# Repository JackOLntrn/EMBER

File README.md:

# EMBER
## Overview
The EMBER project makes use of the a thermal IR camera to detect fires on a pan/tilt motor mechanism. Once a fire is detected, the system points the thermal camera/hose nozzle at the detected fire and activates a solenoid to spray water at the detected fire. The system is supplied with water from a garden hose. This repository includes all of the relavant files for the project. 
| Directory | Contents|
| --- | --- |
| [EMBER/src](src/) | Contains the header and cpp files developed for the project |
| [EMBER/hardware/board](hardware/board) | Contains the schematic board and gerber files used to develop a custom PCB used for the project|
| [EMBER/hardware/mech](hardware/mech) | Contains the 3D model files of parts developed for the project |
| [EMBER/docs](docs/) | Contains doxygen generated documents for code documentation |

See board documentation [here](hardware/board/README.md)

See mechanical component documentation [here](hardware/mech/README.md)

See code documentation [here](https://jackolntrn.github.io/EMBER/)

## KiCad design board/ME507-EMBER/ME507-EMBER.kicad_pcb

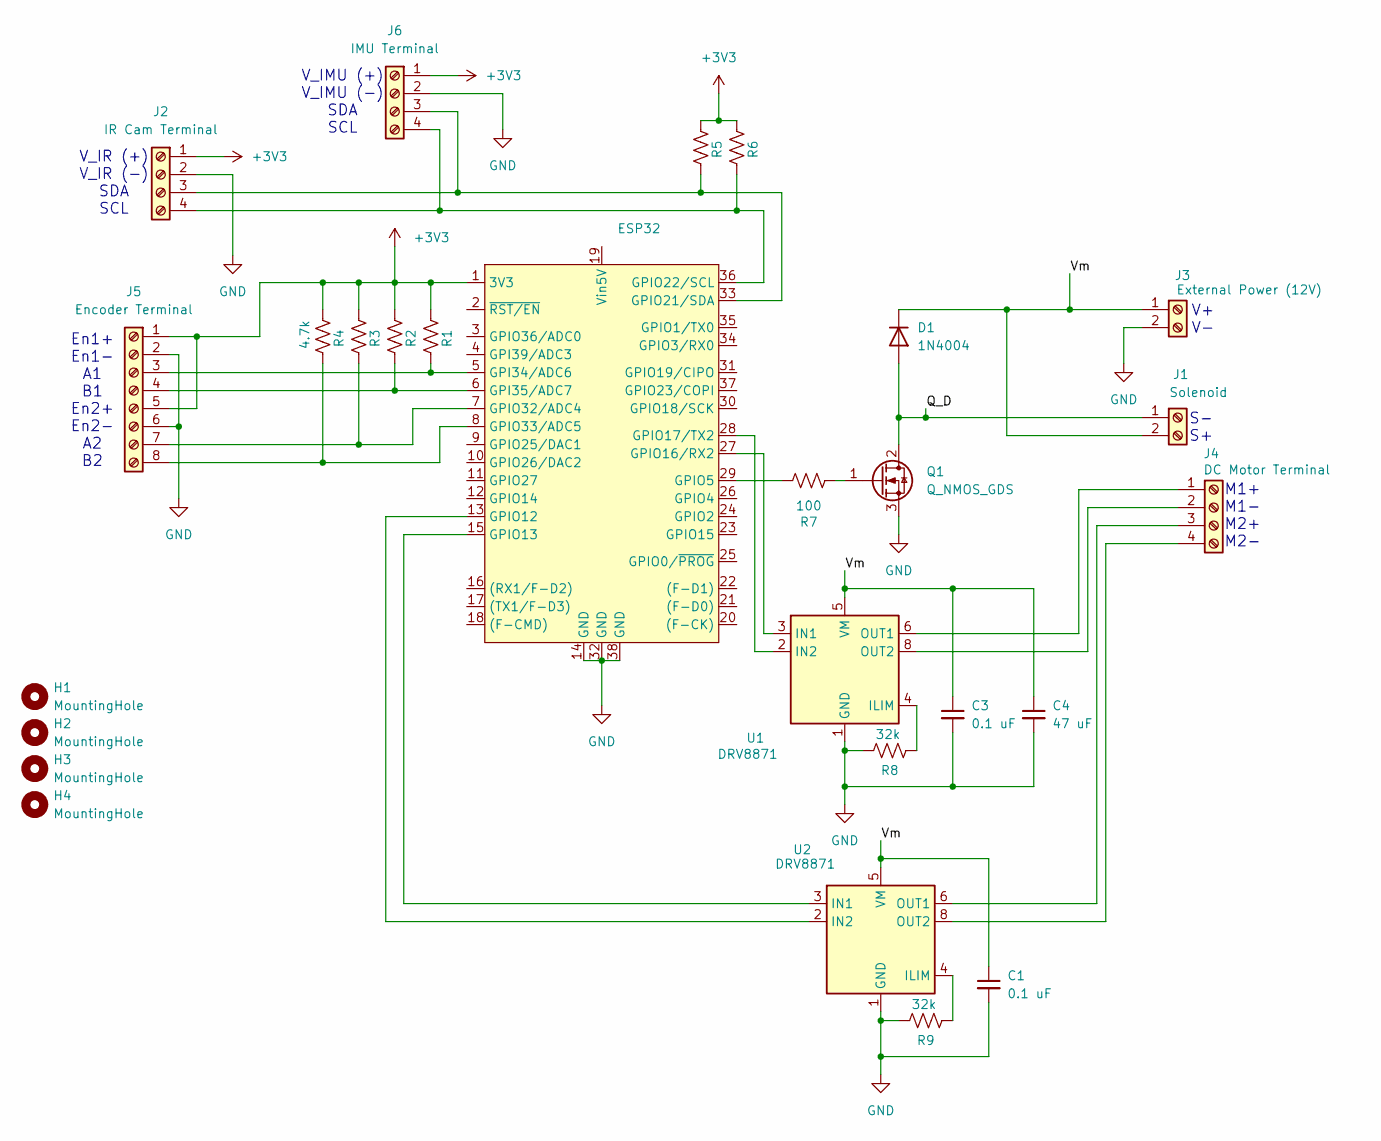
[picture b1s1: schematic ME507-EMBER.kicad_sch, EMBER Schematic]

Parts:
C1, C3: 0.1 uF; C_1206_3216Metric_Pad1.33x1.80mm_HandSolder
C4: 47 uF; C_1206_3216Metric_Pad1.33x1.80mm_HandSolder
D1: 1N4004; D_DO-41_SOD81_P10.16mm_Horizontal
ESP32: ESP32_NodeMCU_KeeYees
H1, H2, H3, H4: MountingHole; MountingHole_2.7mm_M2.5
J1: Solenoid; TerminalBlock_Phoenix_MPT-0,5-2-2.54_1x02_P2.54mm_Horizontal
J2: IR Cam Terminal; TerminalBlock_Phoenix_MPT-0,5-4-2.54_1x04_P2.54mm_Horizontal
J3: External Power (12V); TerminalBlock_Phoenix_MPT-0,5-2-2.54_1x02_P2.54mm_Horizontal
J4: DC Motor Terminal; TerminalBlock_Phoenix_MPT-0,5-4-2.54_1x04_P2.54mm_Horizontal
J5: Encoder Terminal; TerminalBlock_Phoenix_MPT-0,5-8-2.54_1x08_P2.54mm_Horizontal
J6: IMU Terminal; TerminalBlock_Phoenix_MPT-0,5-4-2.54_1x04_P2.54mm_Horizontal
Q1: Q_NMOS_GDS; TO-252-2
R1, R2, R3, R5, R6: R_1206_3216Metric_Pad1.30x1.75mm_HandSolder
R4: 4.7k; R_1206_3216Metric_Pad1.30x1.75mm_HandSolder
R7: 100; R_1206_3216Metric_Pad1.30x1.75mm_HandSolder
R8, R9: 32k; R_1206_3216Metric_Pad1.30x1.75mm_HandSolder
U1, U2: DRV8871; Texas_HTSOP-8-1EP_3.9x4.9mm_P1.27mm_EP2.95x4.9mm_Mask2.4x3.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

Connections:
+3V3: ESP32.1 (3V3), J2.1, J5.1, J5.5, J6.1, R1.2, R2.2, R3.2, R4.2, R5.2, R6.2
/Q_D: D1.2 (A), J1.1, Q1.2 (D)
/Vm: C1.1, C3.1, C4.1, D1.1 (K), J1.2, J3.1, U1.5 (VM), U2.5 (VM)
GND: C1.2, C3.2, C4.2, ESP32.14 (GND), ESP32.32 (GND), ESP32.38 (GND), J2.2, J3.2, J5.2, J5.6, J6.2, Q1.3 (S), R8.1, R9.1, U1.1 (GND), U1.7 (GND), U1.9 (GND), U2.1 (GND), U2.7 (GND), U2.9 (GND)
unnamed: ESP32.5 (GPI34/ADC6), J5.3, R1.1
unnamed: ESP32.6 (GPI35/ADC7), J5.4, R2.1
unnamed: ESP32.29 (GPIO5), R7.1
unnamed: ESP32.13 (GPIO12), U2.2 (IN2)
unnamed: ESP32.15 (GPIO13), U2.3 (IN1)
unnamed: ESP32.27 (GPIO16/RX2), U1.3 (IN1)
unnamed: ESP32.28 (GPIO17/TX2), U1.2 (IN2)
unnamed: ESP32.33 (GPIO21/SDA), J2.3, J6.3, R5.1
unnamed: ESP32.36 (GPIO22/SCL), J2.4, J6.4, R6.1
unnamed: ESP32.7 (GPIO32/ADC4), J5.7, R3.1
unnamed: ESP32.8 (GPIO33/ADC5), J5.8, R4.1
unnamed: J4.1, U1.6 (OUT1)
unnamed: J4.2, U1.8 (OUT2)
unnamed: J4.3, U2.6 (OUT1)
unnamed: J4.4, U2.8 (OUT2)
unnamed: Q1.1 (G), R7.2
unnamed: R8.2, U1.4 (ILIM)
unnamed: R9.2, U2.4 (ILIM)

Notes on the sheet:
M1+ M1- M2+ M2-
V+ V-
En1+ En1- A1 B1 En2+ En2- A2 B2
S- S+
V_IR (+) V_IR (-) SDA SCL
V_IMU (+) V_IMU (-) SDA SCL

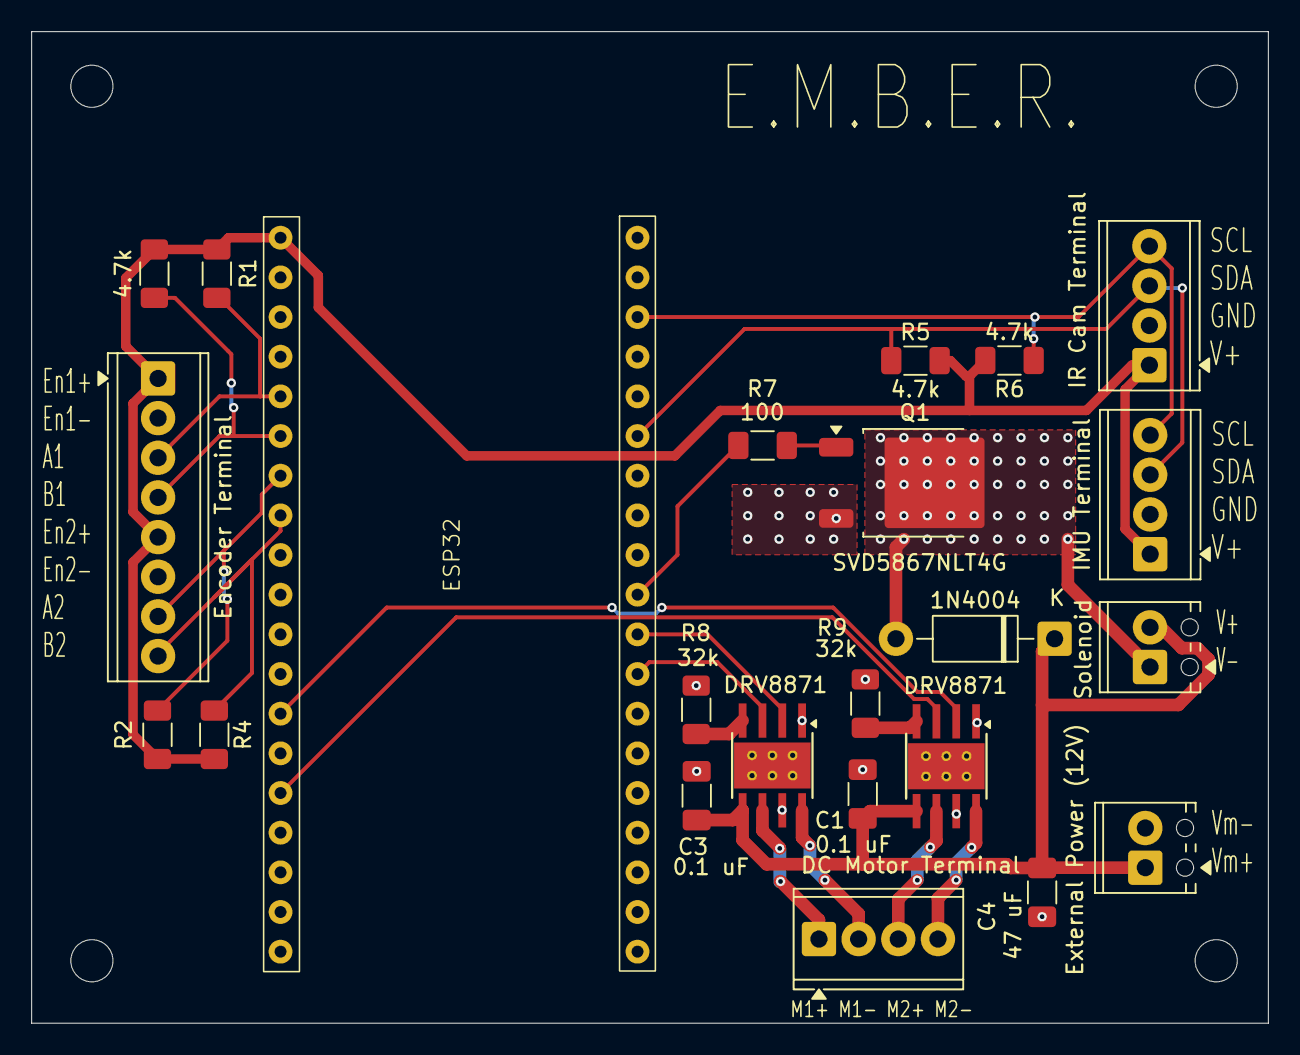
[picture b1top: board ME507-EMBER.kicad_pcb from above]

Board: 2 copper layers, 79.2 x 63.5 mm, 27 parts (0 on the bottom side), 22 nets.

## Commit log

2025-10-09 new file: EMBER/.gitignore new file: EMBER/.vscode/extensions.json new file: EMBER/include/README new file: EMBER/lib/README new file: EMBER/platformio.ini new file: EMBER/src/main.cpp new file: EMBE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
2025-10-09 modified: EMBER/src/main.cpp
2025-10-09 modified: EMBER/platformio.ini
2025-10-10 modified: EMBER/platformio.ini modified: EMBER/src/main.cpp
2025-10-16 deleted: board/EMBER.kicad_sch new file: board/ME507-EMBER/ME507-EMBER-backups/ME507-EMBER-2025-10-03_110047.zip new file: board/ME507-EMBER/ME507-EMBER-backups/ME507-EMBER-2025-10-08_101237.zip new 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
2025-10-17 modified: EMBER/platformio.ini modified: EMBER/src/main.cpp new file: board/ME507-EMBER/ME507-EMBER.kicad_pro new file: board/ME507-EMBER/ME507-EMBER.kicad_sch
2025-10-17 new file: board/ME507-EMBER/~ME507-EMBER.kicad_sch.lck
2025-10-17 modified: board/ME507-EMBER/ME507-EMBER.kicad_sch deleted: board/ME507-EMBER/~ME507-EMBER.kicad_sch.lck
2025-10-23 modified: EMBER/src/main.cpp new file: board/ME507-EMBER/ME507-EMBER-backups/ME507-EMBER-2025-10-19_140626.zip modified: board/ME507-EMBER/ME507-EMBER.kicad_sch
2025-10-24 new file: board/ME507-EMBER/ME507-EMBER-backups/ME507-EMBER-2025-10-23_172612.zip modified: board/ME507-EMBER/ME507-EMBER.kicad_pcb modified: board/ME507-EMBER/ME507-EMBER.kicad_prl modified: board/M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
2025-10-25 new file: board/ME507-EMBER/EMBER_Footprints.pretty/EMBER_Vishay_PowerPAK_1212-8.kicad_mod new file: board/ME507-EMBER/EMBER_Footprints.pretty/MOSFET_Vishay_PowerPAK_1212-8_Single_JACKSON.kicad_mod n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
2025-10-28 deleted: board/ME507-EMBER/ME507-EMBER-backups/ME507-EMBER-2025-10-24_173205.zip new file: board/ME507-EMBER/ME507-EMBER-backups/ME507-EMBER-2025-10-24_181717.zip new file: board/ME507-EMBER/ME507-EM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
2025-10-30 new file: board/ME507-EMBER/ME507-EMBER-backups/ME507-EMBER-2025-10-30_154305.zip new file: board/ME507-EMBER/ME507-EMBER-backups/ME507-EMBER-2025-10-30_160009.zip new file: board/ME507-EMBER/ME507-E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
2025-11-06 modified: EMBER/src/main.cpp new file: board/ME507-EMBER/EmberGerb.zip new file: board/ME507-EMBER/EmberGerb/ME507-EMBER-B_Cu.gbl new file: board/ME507-EMBER/EmberGerb/ME507-EMBER-B_Mask.gbs new file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
2025-11-07 new file: EMBER/src/DRV8871Driver.cpp new file: EMBER/src/DRV8871Driver.h modified: EMBER/src/main.cpp DRV8871Driver to control motor driver, needs to be tested.
2025-11-07 modified: EMBER/platformio.ini modified: EMBER/src/DRV8871Driver.h modified: EMBER/src/main.cpp
2025-11-07 modified: EMBER/src/DRV8871Driver.cpp modified: EMBER/src/DRV8871Driver.h modified: EMBER/src/main.cpp
2025-11-10 modified: EMBER/src/DRV8871Driver.cpp modified: EMBER/src/DRV8871Driver.h new file: board/ME507-EMBER/ME507-EMBER-backups/ME507-EMBER-2025-11-06_174039.zip modified: board/ME507-EMBER/ME507-EMBER.kic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
2025-11-10 modified: EMBER/platformio.ini modified: EMBER/src/DRV8871Driver.cpp modified: EMBER/src/DRV8871Driver.h modified: EMBER/src/main.cpp
2025-11-14 modified: EMBER/platformio.ini modified: EMBER/src/main.cpp new file: EMBER/src/shares.h new file: EMBER/src/task_motorControl.cpp new file: EMBER/src/task_motorControl.h new file: EMBER/src/task_tem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
2025-11-21 modified: EMBER/platformio.ini modified: EMBER/src/main.cpp new file: EMBER/src/task_read_camera.cpp new file: EMBER/src/task_read_camera.h
2025-12-03 modified: EMBER/platformio.ini modified: EMBER/src/main.cpp modified: EMBER/src/task_read_camera.cpp modified: EMBER/src/task_read_camera.h new file: EMBER/src/task_webserver.cpp new file: EMBER/src/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
2025-12-03 modified: EMBER/src/main.cpp modified: EMBER/src/shares.h modified: EMBER/src/task_motorControl.cpp modified: EMBER/src/task_read_camera.cpp new file: EMBER/src/task_stateMachine.cpp new file: EMBER/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
2025-12-04 modified: EMBER/platformio.ini modified: EMBER/src/main.cpp modified: EMBER/src/shares.h modified: EMBER/src/task_motorControl.cpp modified: EMBER/src/task_read_camera.cpp modified: EMBER/src/task_re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
2025-12-04 modified: EMBER/src/task_motorControl.cpp modified: EMBER/src/task_read_camera.cpp modified: EMBER/src/task_stateMachine.cpp modified: EMBER/src/task_webserver.cpp deleted: board/ME507-EMBER/~ME507-E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
2025-12-05 modified: EMBER/src/main.cpp modified: EMBER/src/shares.h modified: EMBER/src/task_motorControl.cpp modified: EMBER/src/task_read_camera.cpp modified: EMBER/src/task_stateMachine.cpp modified: EMBER/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
2025-12-05 modified: EMBER/src/main.cpp modified: EMBER/src/task_motorControl.cpp modified: EMBER/src/task_read_camera.cpp modified: EMBER/src/task_stateMachine.cpp modified: EMBER/src/task_webserver.cpp
2025-12-06 hardware folder for board and cad
2025-12-06 somehow i can't make a folder
2025-12-08 deleted: board/ME507-EMBER/EmberGerb.zip renamed: board/ME507-EMBER/EMBER_Footprints.pretty/EMBER_Vishay_PowerPAK_1212-8.kicad_mod -> hardware/board/EMBER_Footprints.pretty/EMBER_Vishay_PowerPAK_1212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
2025-12-08 deleted: EMBER/hardware/board/README
2025-12-08 new file: docs/README.md
2025-12-08 modified: platformio files/platformio.ini modified: src/DRV8871Driver.cpp modified: src/DRV8871Driver.h modified: src/task_motorControl.cpp modified: src/task_motorControl.h modified: src/task_read_c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
2025-12-08 modified: src/main.cpp
2025-12-09 Add heading to README.md
2025-12-09 new file: hardware/board/Board.pdf new file: hardware/board/Schematic.pdf
2025-12-09 Enhance README with project overview and structure
    Added project overview and file structure details.
2025-12-09 Enhance README with project file structure table
    Added a table to the README for project file organization.
2025-12-09 Enhance README with project contents table
    Added a table to the README for better organization of project contents.
2025-12-09 Fix spelling and format in README.md
    Corrected spelling of 'relevant' and improved formatting.
2025-12-09 Add links to hardware documentation
    Added hardware documentation links to README.
2025-12-09 Update hardware documentation links in README
2025-12-09 Add README.md with header in mech directory
2025-12-09 Revise README with EMBER mechanical components details
    Updated the README to include detailed descriptions of EMBER mechanical components and their assembly files.
2025-12-09 Revise component descriptions in README.md
    Updated descriptions for EMBER components in README.
2025-12-09 Enhance README with component details and new sections
    Updated README to clarify component descriptions and added sections for custom Solidworks files and electrical hardware.
2025-12-09 Fix links and add quantities in hardware README
    Updated links and added quantities for mechanical hardware components in the README.
2025-12-09 Update README with directory links for navigation
2025-12-09 Fix directory path in README for SRC folder
2025-12-09 Fix directory paths in README.md
    Corrected directory paths in the README file for consistency.
2025-12-09 Fix formatting of platformio files link in README
2025-12-09 Update README with hardware components and quantities
2025-12-09 Fix item numbering in hardware/mech README
    Updated item numbering for clarity in the README.
2025-12-09 Update README with component details and quantities
    Added detailed descriptions and quantities for various components of the EMBER project, including mechanical parts and electrical hardware.
2025-12-09 Create pictures folder
2025-12-09 new file: docs/html/_d_r_v8871_driver_8cpp.html new file: docs/html/_d_r_v8871_driver_8h_source.html new file: docs/html/annotated.html new file: docs/html/annotated_dup.js new file: docs/html/class_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
    new file: docs/html/class_d_r_v8871_driver.html
    new file: docs/html/class_d_r_v8871_driver.js
    new file: docs/html/classes.html
    new file: docs/html/clipboard.js
    new file: docs/html/cookie.js
    new file: docs/html/dir_68267d1309a1af8e8297ef4c3efbcdba.html
2025-12-09 new file: docs/Doxyfile renamed: docs/html/_d_r_v8871_driver_8cpp.html -> docs/docs/_d_r_v8871_driver_8cpp.html renamed: docs/html/_d_r_v8871_driver_8h_source.html -> docs/docs/_d_r_v8871_driver_8h_s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
2025-12-09 Update README with images and descriptions for parts
2025-12-09 new file: docs/docs/_d_r_v8871_driver_8cpp.html new file: docs/docs/_d_r_v8871_driver_8h_source.html new file: docs/docs/annotated.html new file: docs/docs/annotated_dup.js new file: docs/docs/class_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
2025-12-09 renamed: docs/docs/_d_r_v8871_driver_8cpp.html -> docs/_d_r_v8871_driver_8cpp.html renamed: docs/docs/_d_r_v8871_driver_8h_source.html -> docs/_d_r_v8871_driver_8h_source.html renamed: docs/docs/anno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
2025-12-09 new file: hardware/board/Board_3D.png
2025-12-09 new file: docs/docs/_d_r_v8871_driver_8cpp.html new file: docs/docs/_d_r_v8871_driver_8h.html new file: docs/docs/_d_r_v8871_driver_8h.js new file: docs/docs/_d_r_v8871_driver_8h_source.html new file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
2025-12-09 modified: docs/_d_r_v8871_driver_8cpp.html renamed: docs/docs/_d_r_v8871_driver_8h.html -> docs/_d_r_v8871_driver_8h.html renamed: docs/docs/_d_r_v8871_driver_8h.js -> docs/_d_r_v8871_driver_8h.js mo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
2025-12-09 Create CNAME
2025-12-09 modified: docs/dir_68267d1309a1af8e8297ef4c3efbcdba.html modified: docs/files.html modified: docs/task__motor_control_8h.html modified: docs/task__motor_control_8h_source.html modified: docs/task__re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
2025-12-09 modified: src/task_motorControl.cpp modified: src/task_motorControl.h modified: src/task_read_camera.cpp modified: src/task_stateMachine.cpp modified: src/task_stateMachine.h
2025-12-09 modified: docs/task__motor_control_8cpp.html modified: docs/task__motor_control_8h.html modified: docs/task__motor_control_8h_source.html modified: docs/task__read__camera_8h.html modified: docs/task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
2025-12-09 modified: docs/dir_68267d1309a1af8e8297ef4c3efbcdba.html modified: docs/dir_68267d1309a1af8e8297ef4c3efbcdba.js modified: docs/doxygen_crawl.html modified: docs/files.html modified: docs/globals.html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
